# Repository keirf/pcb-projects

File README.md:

# PCB Projects: KiCad Designs for Retro Projects

## Documentation

- [**Kickstart Switcher**](https://github.com/keirf/pcb-projects/wiki/Kickstart-Switcher-v2)
  Assembly instructions and installation guide
- [**EPROM Adapter**](https://github.com/keirf/pcb-projects/wiki/EPROM-Adapter-v4)
  Usage instructions for all versions of this adapter

The old Kickstart switcher documentation is
[here](https://github.com/keirf/pcb-projects/wiki/Kickstart-Switcher-v1).

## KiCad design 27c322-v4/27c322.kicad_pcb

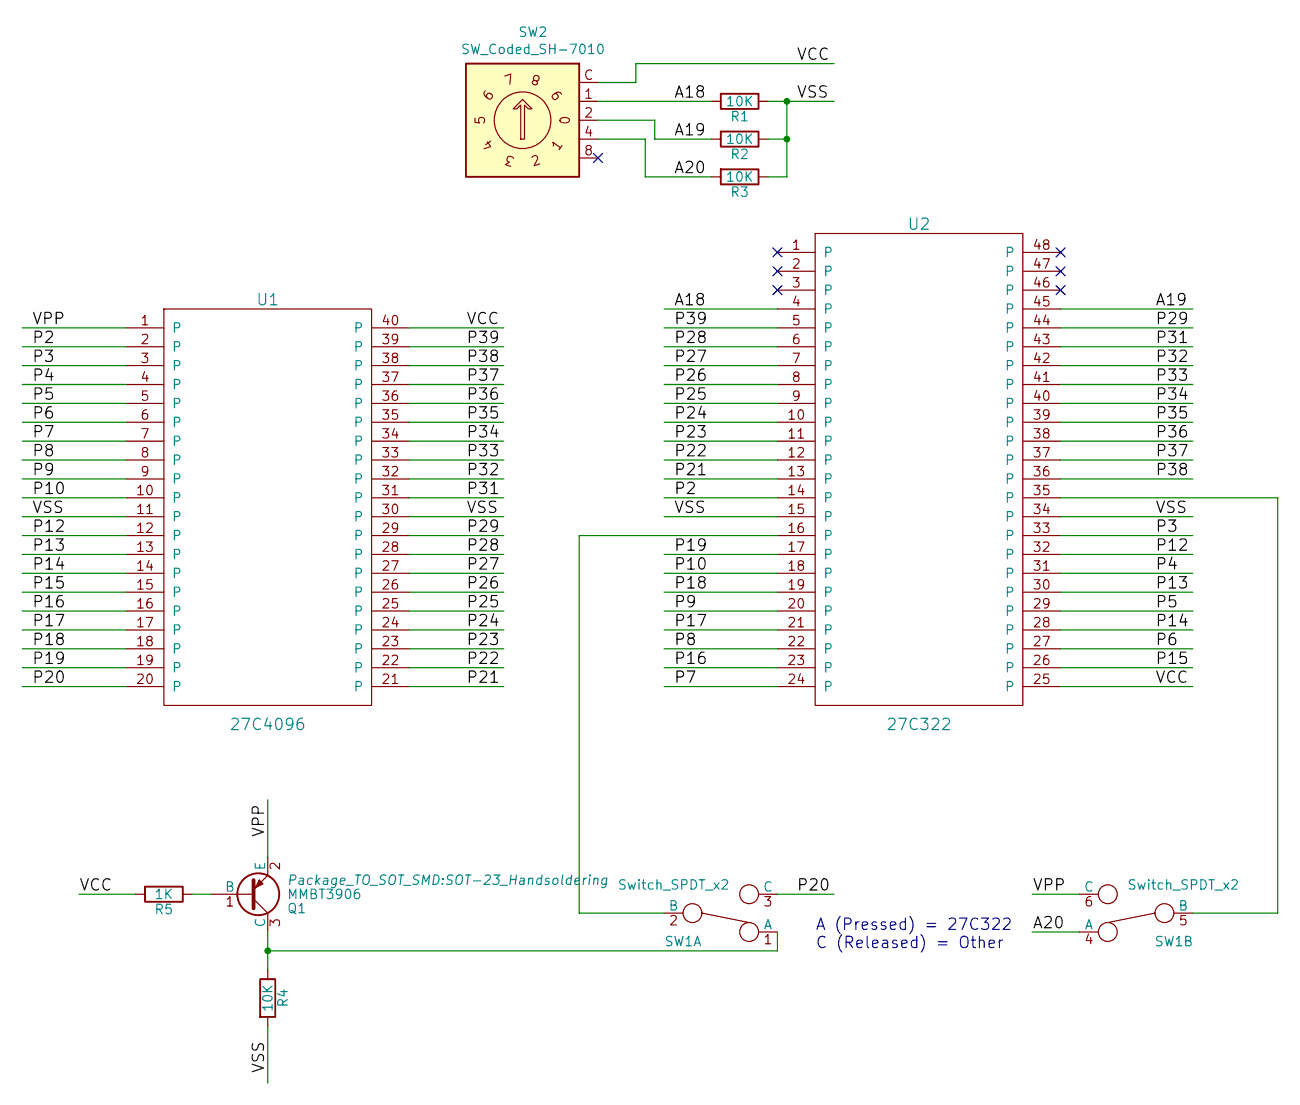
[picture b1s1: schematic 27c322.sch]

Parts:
Q1: MMBT3906; SOT-23_Handsoldering
R1, R2, R3, R4: 10K; R_0805_2012Metric_Pad1.15x1.40mm_HandSolder
R5: 1K; R_0805_2012Metric_Pad1.15x1.40mm_HandSolder
SW1: Switch_SPDT_x2; DPDT_Slide
SW2: SW_Coded_SH-7010; Rotary_Switch
U1: 27C4096
U2: 27C322; 27C160

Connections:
/A18: R1.2, SW2.1, U2.4
/A19: R2.2, SW2.2, U2.45
/A20: R3.2, SW1.4 (A), SW2.4
/P2: U1.2, U2.14
/P3: U1.3, U2.33
/P4: U1.4, U2.31
/P5: U1.5, U2.29
/P6: U1.6, U2.27
/P7: U1.7, U2.24
/P8: U1.8, U2.22
/P9: U1.9, U2.20
/P10: U1.10, U2.18
/P12: U1.12, U2.32
/P13: U1.13, U2.30
/P14: U1.14, U2.28
/P15: U1.15, U2.26
/P16: U1.16, U2.23
/P17: U1.17, U2.21
/P18: U1.18, U2.19
/P19: U1.19, U2.17
/P20: SW1.3 (C), U1.20
/P21: U1.21, U2.13
/P22: U1.22, U2.12
/P23: U1.23, U2.11
/P24: U1.24, U2.10
/P25: U1.25, U2.9
/P26: U1.26, U2.8
/P27: U1.27, U2.7
/P28: U1.28, U2.6
/P29: U1.29, U2.44
/P31: U1.31, U2.43
/P32: U1.32, U2.42
/P33: U1.33, U2.41
/P34: U1.34, U2.40
/P35: U1.35, U2.39
/P36: U1.36, U2.38
/P37: U1.37, U2.37
/P38: U1.38, U2.36
/P39: U1.39, U2.5
/VCC: R5.2, SW2.C, U1.40, U2.25
/VPP: Q1.2 (E), SW1.6 (C), U1.1
/VSS: R1.1, R2.1, R3.1, R4.2, U1.11, U1.30, U2.15, U2.34
unnamed: Q1.1 (B), R5.1
unnamed: Q1.3 (C), R4.1, SW1.1 (A)
unnamed: SW1.2 (B), U2.16
unnamed: SW1.5 (B), U2.35

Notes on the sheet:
A (Pressed) = 27C322 C (Released) = Other

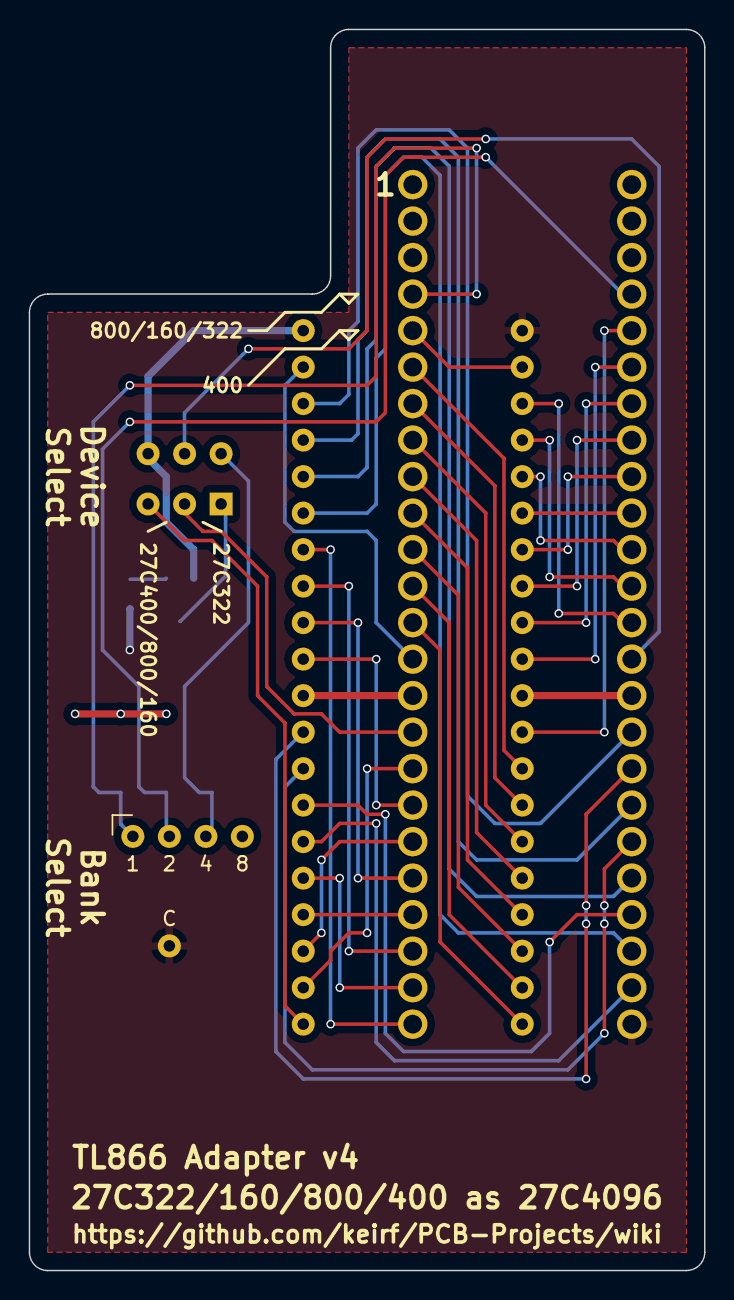
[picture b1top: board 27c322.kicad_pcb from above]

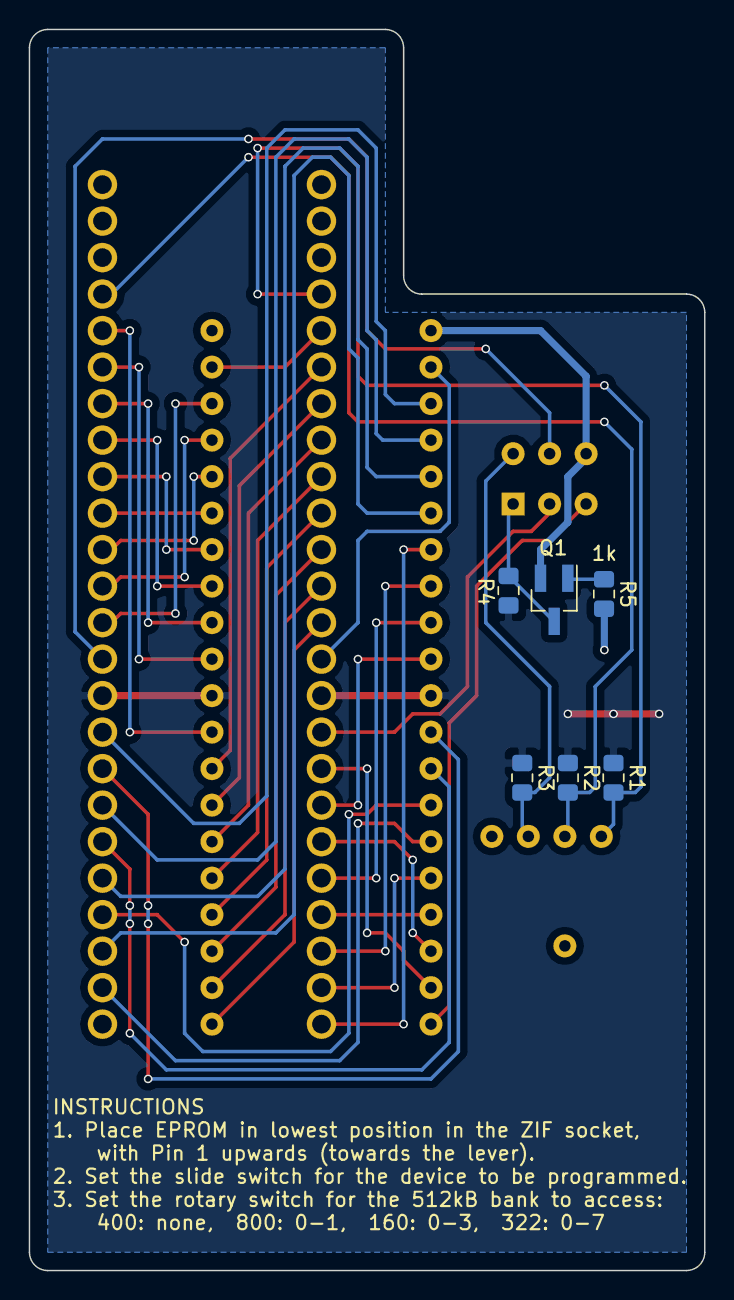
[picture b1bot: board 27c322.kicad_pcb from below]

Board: 2 copper layers, 47.0 x 86.4 mm, 10 parts (6 on the bottom side), 46 nets.

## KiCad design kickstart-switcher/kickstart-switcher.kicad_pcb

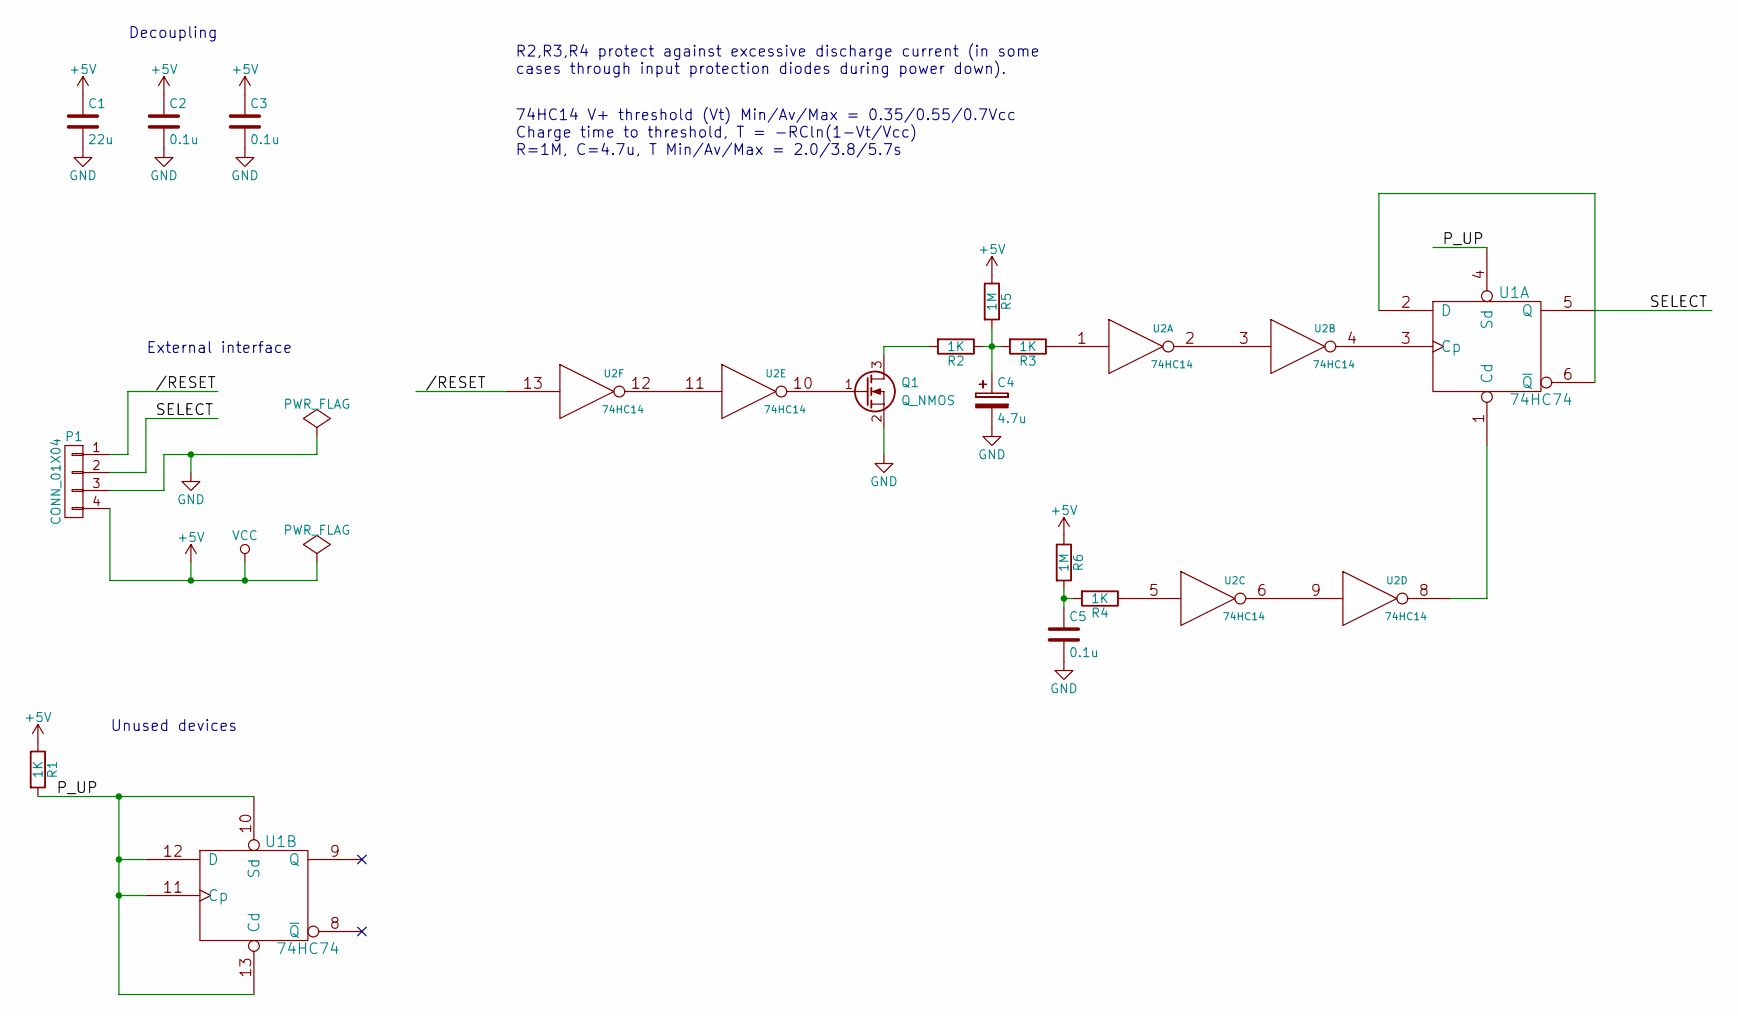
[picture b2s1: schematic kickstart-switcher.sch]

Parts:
C1: 22u; R_0805_HandSoldering
C2, C3, C5: 0.1u; R_0805_HandSoldering
C4: 4.7u; R_0805_HandSoldering
P1: CONN_01X04; Pin_Header_Straight_1x04
Q1: Q_NMOS; SOT-23_Handsoldering
R1, R2, R3, R4: 1K; R_0805_HandSoldering
R5, R6: 1M; R_0805_HandSoldering
U1: 74HC74; SOIC-14_N
U2: 74HC14; SOIC-14_N

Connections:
//RESET: P1.1, U2.13
/P_UP: R1.2, U1.4 (Sd), U1.10 (Sd), U1.11 (Cp), U1.12 (D), U1.13 (Cd)
/SELECT: P1.2, U1.5 (Q)
GND: C1.2, C2.2, C3.2, C4.2, C5.2, P1.3, Q1.2 (S), U1.7 (GND), U2.7 (GND)
unnamed: C4.1, R2.1, R3.2, R5.2
unnamed: C5.1, R4.2, R6.2
unnamed: Q1.1 (G), U2.10
unnamed: Q1.3 (D), R2.2
unnamed: R3.1, U2.1
unnamed: R4.1, U2.5
unnamed: U1.1 (Cd), U2.8
unnamed: U1.2 (D), U1.6 (~Q)
unnamed: U1.3 (Cp), U2.4
unnamed: U2.2, U2.3
unnamed: U2.6, U2.9
unnamed: U2.11, U2.12
VCC: C1.1, C2.1, C3.1, P1.4, R1.1, R5.1, R6.1, U1.14 (VCC), U2.14 (VCC)

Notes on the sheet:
Decoupling
Unused devices
External interface
74HC14 V+ threshold (Vt) Min/Av/Max = 0.35/0.55/0.7Vcc Charge time to threshold, T = -RCln(1-Vt/Vcc) R=1M, C=4.7u, T Min/Av/Max = 2.0/3.8/5.7s
R2,R3,R4 protect against excessive discharge current (in some cases through input protection diodes during power down).

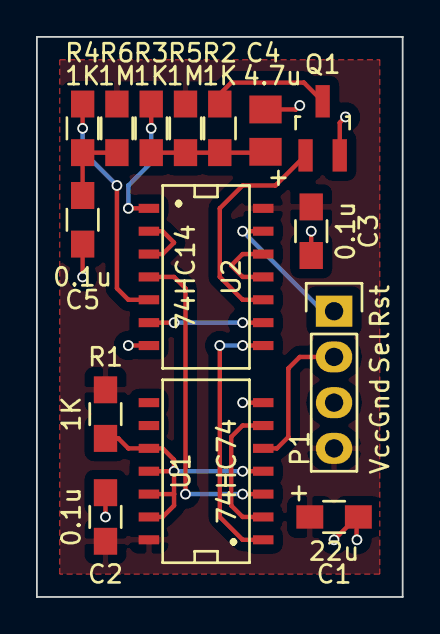
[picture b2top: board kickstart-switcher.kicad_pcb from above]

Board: 2 copper layers, 20.3 x 31.1 mm, 15 parts (0 on the bottom side), 17 nets.

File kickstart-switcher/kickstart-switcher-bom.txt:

REF         PART DESCRIPTION                   RS ORDER
===         ================                   ========
C1          22uF MLCC (0805)                   820-2765
C2,C3,C5    0.1uF MLCC (0805)                  390-990
C4          4.7uF Tantalum (2012)              547-9760
R1-R4       1K 5% (0805)                       
R5-R6       1M 5% (0805)                       618-3729
Q1          N-Channel MOSFET (SOT-23)          780-4742
U1          74HC74 (SOIC)                      526-347
U2          74HC14 (SOIC)                      526-577

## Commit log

2015-07-22 27c400-adaptor: 27c400->27c4096 (JEDEC) amstrad-26pin-adaptor: Amstrad host -> PC Floppy
    Panelisation of both above, plus FlashFloppy-MM150, onto
    a 10x10cm board
2015-08-22 New panelisation of the 27c400 adaptor + amstrad adaptor, 2 up. Place panelisations in their own folder. Fold Amstrad silks changes into the base amstrad layout file.
2015-09-16 27c160-adaptor: 27c160/800/400->27c4096 (JEDEC)
2015-09-16 2-up panelisation of 27c160-adaptor to 10cmx10cm board
2016-04-22 kickstart-switcher: Small two-way Amiga Kickstart switcher, based on long reset (Ctrl-Amiga-Amiga for around 5 seconds).
    Includes 12-up 10cmx10cm panelisation.
2016-04-22 git: Ignore some kicad-generated files.
2016-04-22 panels: Extend the README a little
2016-04-22 kickstart-switcher: Add 1K protection resistors to RC delay HCMOS inputs. Prevents excessive current through over-voltage diodes on power down.
2016-05-09 Pull footprint library into a single shared repo-wide location.
2016-05-20 kickstart-switcher: Use second 74HC74 flip-flop to generate extra select line and allow 4-way image selection
2016-06-04 27c322-adapter: 27C322/160/800/300 -> 27C4096 (JEDEC)
2016-06-07 panels: 2-up 10cmx10cm panelisation of the 27C322 adapter board
2016-08-07 docs/kickstart-switcher: Add assembly/installation instructions
2016-08-07 docs: Prettify the formatting a little.
2016-08-08 docs: Simplify the kickstart switcher instructions
2016-08-08 docs: Instructions on using the EPROM adapter series
2016-08-10 README: Improve layout
2016-08-13 27c322: Reduce R3 value to 1K in schematic
2016-08-14 docs/eprom-adapter: Add a troubleshooting guide/
2016-08-14 docs/eprom-adapter: Suggest leaving VPP=13.50V in all cases.
2016-08-20 docs/eprom-adapter: Less strong recommendation for VPP=13.5V. Not clear how much better it is than 12.5V, really.
2017-04-15 docs/eprom-adapter: Provide some brief self-assembly guidelines.
2017-05-25 kickstart-switcher: Move old project under v1/ sub-directory
2017-06-06 kickstart-switcher: New design based on STM32F103C8T6 dev board
2017-06-12 kickstart-switcher: v2.1, allow configuration via serial line
2017-06-16 kickstart-switcher: Better exception logging. Allow unaligned accesses.
2017-06-18 kickstart-switcher: Update v2 docs
2017-06-19 kickstart-switcher: v2.2: Fix serial terminal CR/LF behaviour
2017-06-19 kickstart-switcher: Update docs to mention PuTTY for Windows
2017-06-19 docs: Mention PL2303HX USB-TTL chipset and Windows workaround.
2017-06-22 docs: Show correct switch orientation for 27c322 eprom adapter
2017-06-29 stm32f1: More care over NVIC setup and barriers around IRQ disable.
2017-06-30 kickstart-switcher: Fixes to the speaker code. 1. Must set CCxE only after setting CC mode 2. Remove bogus write of CCRx.
2017-07-01 stm32: Some more changes to initialisation: 1. Setup and switch to Process SP must be atomic wrt SP updates. 2. No need to init NVIC nor PRIMASK/FAULTMASK as they have known reset values.
2017-07-06 kickstart-switcher: Simplify the main switch logic and reset-line sampling a little.
2017-07-06 kickstart-switcher: Update to v2.3
2017-08-11 vsnprintf: Output string must always be nul-terminated
2017-08-11 console: Remove asynchronous DMA-driven mode. We weren't using it anyway.
2017-08-11 kickstart-switcher: Update to v2.4
2017-09-27 docs: Move to Github wiki
2019-02-28 amstrad-26: Clean up board silks
2019-02-28 27c322-v4: Initial rev
2019-03-01 kickstart-switcher: v2.5, supports image recall
2019-03-04 kickstart-switcher: Asynchronous serial, and 32-bit time.
2019-03-04 kickstart-switcher: Greatly reduce settling time for detecting jumpered pins. A few microseconds is plenty.
2019-03-04 kickstart-switcher: Change the last-recall algorithm and bump to v2.6
2019-03-26 kswitch: Emit long beep for each multiple of four images.
2019-05-24 ff-test-adapter
2019-05-24 panellised 27c322-v4 and ff-test adapter
2019-07-08 Update README link
2019-10-10 stm32: Update register defs
2019-10-15 Greaseweazle adapter PCBs.
2020-01-22 CC0 license
2021-04-03 Bill of Materials for F1 Greaseweazle Fixes #2
2021-04-03 greaseweazle: Update BoM to make clear USBPU is conditional on BP modification Refs #2
2021-12-06 kswitch: Fix build for recent GCC
2021-12-06 Initial patches to target STM32F103C6 low density chip
2021-12-23 Repo names renamed to all lower case
